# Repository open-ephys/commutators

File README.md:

> [!Important]  
> This repository has been split into dedicated repositories for each design:
>
>  - https://github.com/open-ephys/commutator-coax
>  - https://github.com/open-ephys/commutator-spi
>  - https://github.com/open-ephys/commutator-dual
>  - etc.
>
> Future commutator designs, issue tracking, etc. will take place in those repositories.
> This repository is deprecated.

# Torque-free commutators for orientation-aware headstages and miniscopes
The wide-spread availability of 6 degree of freedom pose tracking using
internal-measurement units (IMUs) allows continuous monitoring of an animal's
rotational state in an environment. This obviates the need for tether torque
measurements to drive an active commutator since the rotational state of the
animal is known in real-time, and the commutator can simply follow along. This
permits the use of extremely thin [coaxial
tethers](http://www.axon-cable.com/en/02_products/06_coaxial-cables/02/index.aspx)
that cannot function with a standard active commutator because they are too
flexible to translate rotational torque.

This commutator functions with headstages and miniscopes that provide
provide appropriate rotational tracking information. Currently
supported devices are next-generation, serialized headstages and miniscopes
such as [ONIX headstages](https://open-ephys.github.io/onix-docs/index.html), 
and UCLA Miniscope 4.0, and Open Ephys 3D low-profile SPI headstages.
However, this device operations completely independently from the headstage
itself, so can be used with any device that provides accurate, drift-free
rotational state. It can even be used without an IMU, e.g. using video-based
rotation tracking since its remote control interface is agnostic to how
rotational measurements are taken.

## Features
- Variants for high bandwidth RF links up to 18 GHz and low-bandwidth SPI cables
- Optical table & 80/20 rail mountable
- Remote control using JSON-encoded commands
- Manual control using capacitive sense buttons
- Indication LED
    - Can be completely turned off
- Advanced stepper driver (TMC2130)
    - Voltage-controlled for silent operation
    - Precise motion using step interpolation (256 uSteps/step)
- USB powered and controlled
    - Internal super-capacitor circuitry prevents loading the USB bus during
      motion

## Usage

**Note**: A high-quality, within-spec micro USB cable must be used when connecting 
the commutator to the host computer.

### LED
The LED tells you about the commutator state:

1. Flashing red (*Charging*): commutator is charging internal super-capacitors.
   All controls and motor operation are locked. Wait until this process
   completes to use the device. It can take up to 30 seconds.
1. Solid red (*Disabled*): commutator is disabled. Motor is turned off and will not
   turn or respond to button presses or external commands.
1. Green (*Enabled*): commutator is enabled and permits both remote and manual
   (button) turn control. Buttons take precedence over remote commands.

### Buttons
The front panel has four buttons.

- __Enable/Disable__: toggle commutator enable/disable.
    - *Disabled* (LED is red): All motor output will halt instantly, and motor
      driver is powered down. Pressing directional buttons in the stopped state
      will not work. All target turns provided via remote calls will be
      cleared, such that re-enable the motor will not result in the commutator
      re-engaging an old target position. In this state, pressing 
      the Enable/Disable button, or sending the approriate remote
      command, will enable the device.
    - *Enabled* (LED  green): When in the *enabled* state, the LED will be
      green and the motor can be turned via button presses or RPCs . In this
      state, pressing the Stop/Go button, or sending the approriate remote
      command, will instantly disable the device.

- __Directional__ (2x): Manually control the motor rotation in the
  direction indicated on each button when the commutator is *Enabled*. These
  inputs take precedence over and override ongoing remote motor control.  When
  pressed, all target turns provided via remote control will be cleared, such
  that releasing them will not result in the commutator re-engaging an old
  target position. Remote commands sent when a button is being pressed are
  ignored.

- __LED__: pressing the LED will toggled on and off (e.g for cases where it presents an
  unwanted visual stimulus).

### Remote control interface
When manual buttons are not being pressed, the commutator accepts JSON-encoded
commands over its serial interface. Here are examples of all commands that can
be sent:
```
{enable : true}     // Enable commutator (default = false)
{led : false}       // Turn off RGB LED (default = true)
{speed : 250}       // Set turn speed to 250 RPM (default = 50 RPM, valid ∈ (0, 500] RPM)
{turn : 1.1}        // 1.1 turns CW
{turn : -1.1}       // 1.1 turns CCW

// Example multi-command. Any combo can be used.
// In this case:
// 1. Turn LED off
// 1. Set speed to 25 RPM
// 2. Excecute 1.1 turns CC
// Ordering of commands does not matter, it is determined by the firmware
{led: false, speed: 25, turn : -1.1}
```
The communator state can be read using the `{print:}` command  which will
return a JSON object containing version, state, and motor parameters.

### Saving settings
All control and speed parameters, whether changed via the remote or manual
interface, are saved in non-volatile memory each time they are changed. The
device will start in the same state it was last used.

## Firmware
The controller firmware is located [here](./firmware/commutator). It runs on a
[Teensy lc](https://www.pjrc.com/store/teensylc.html). To compile
this firmware and program the microcontroller, you need the following
dependencies:

- [Arduino IDE](https://www.arduino.cc/en/Main/Software)
- [Teensyduino add-on](https://www.pjrc.com/teensy/td_download.html)
- [AccelStepper](https://www.airspayce.com/mikem/arduino/AccelStepper/)
- [Arduino JSON](https://arduinojson.org/)

The firmware can be uploaded to the device using the [Arduino
IDE](https://www.arduino.cc/en/Main/Software). _Note that you will need to add
the [Teensyduino add-on](https://www.pjrc.com/teensy/teensyduino.html) to to
the Arduino IDE to program the Teensy_. When installing Teensyduino, you should
opt to install all of the bundled libraries as well. This takes care of
installing `AccelStepper` library rather than having to install it manually.
ArduinoJSON can be installed through the Arduino IDE's package manager.

## Construction

### Bill of Materials
The BOM is located [here](https://docs.google.com/spreadsheets/d/1M2R0Q2-OuRHzctt05BxtA3hxNcCHtRZHORzCKElmG1Q/edit#gid=1283420334).

### Mechanical
The mechanical component of the commutator are as follows:

1. RF Rotary Joint
1. 2x reduction gears (3D-printed)
1. NEMA-11 Stepper Motor
1. Housing (3D-printed)
1. Some fasteners

Mechanical designs are located [here](./mechanical/). STL files for 3D printing
are located in the `stl` subdirectory. Links to purchase each of these
components, including 3D-printed parts, can be found on the BOM.

### Electronics
The board used to control the commutator consists of the following elements:

1. [Teensy LC](https://www.pjrc.com/store/teensylc.html) for receiving
   commands and controlling all circuit elements.
1. [TMC2130 stepper driver](https://www.analog.com/media/en/technical-documentation/data-sheets/TMC2130_datasheet_rev1.15.pdf) for driving the
   motor.
1. Super-capacitor charge system and step-up regulator for providing
   high-current capacity drive to the motor driver directly from USB.
1. RGB indicator LED.
1. Capacitive touch sensors on the back side of the PCB that serve as buttons
   for manual commutator control

Board designs and manufacturing files are located [here](./pcb/). 

## Hardware License
This license pertains to documents in the `control-board`, `mechanical`, and
`resources` subdirectory.

This work is licensed to Jonathan P. Newman and Jakob Voigts under CC BY-NC-SA
4.0. To view a copy of this license, visit
https://creativecommons.org/licenses/by-nc-sa/4.0

The creation of commercial products using the hardware documentation in this
repository is not permitted without an explicit, supplementary agreement
between the Licensor and the Licensee. Please get in touch if you are
interested in commercially distributing this tool.

## Software/Firmware License
This license pertains to documents in the source code in the `firmware`
subdirectory.

Copyright Jonathan P. Newman

Permission is hereby granted, free of charge, to any person obtaining a copy of
this software and associated documentation files (the "Software"), to deal in
the Software without restriction, including without limitation the rights to
use, copy, modify, merge, publish, distribute, sublicense, and/or sell copies
of the Software, and to permit persons to whom the Software is furnished to do
so, subject to the following conditions:

The above copyright notice and this permission notice shall be included in all
copies or substantial portions of the Software.

THE SOFTWARE IS PROVIDED "AS IS", WITHOUT WARRANTY OF ANY KIND, EXPRESS OR
IMPLIED, INCLUDING BUT NOT LIMITED TO THE WARRANTIES OF MERCHANTABILITY,
FITNESS FOR A PARTICULAR PURPOSE AND NONINFRINGEMENT. IN NO EVENT SHALL THE
AUTHORS OR COPYRIGHT HOLDERS BE LIABLE FOR ANY CLAIM, DAMAGES OR OTHER
LIABILITY, WHETHER IN AN ACTION OF CONTRACT, TORT OR OTHERWISE, ARISING FROM,
OUT OF OR IN CONNECTION WITH THE SOFTWARE OR THE USE OR OTHER DEALINGS IN THE
SOFTWARE.

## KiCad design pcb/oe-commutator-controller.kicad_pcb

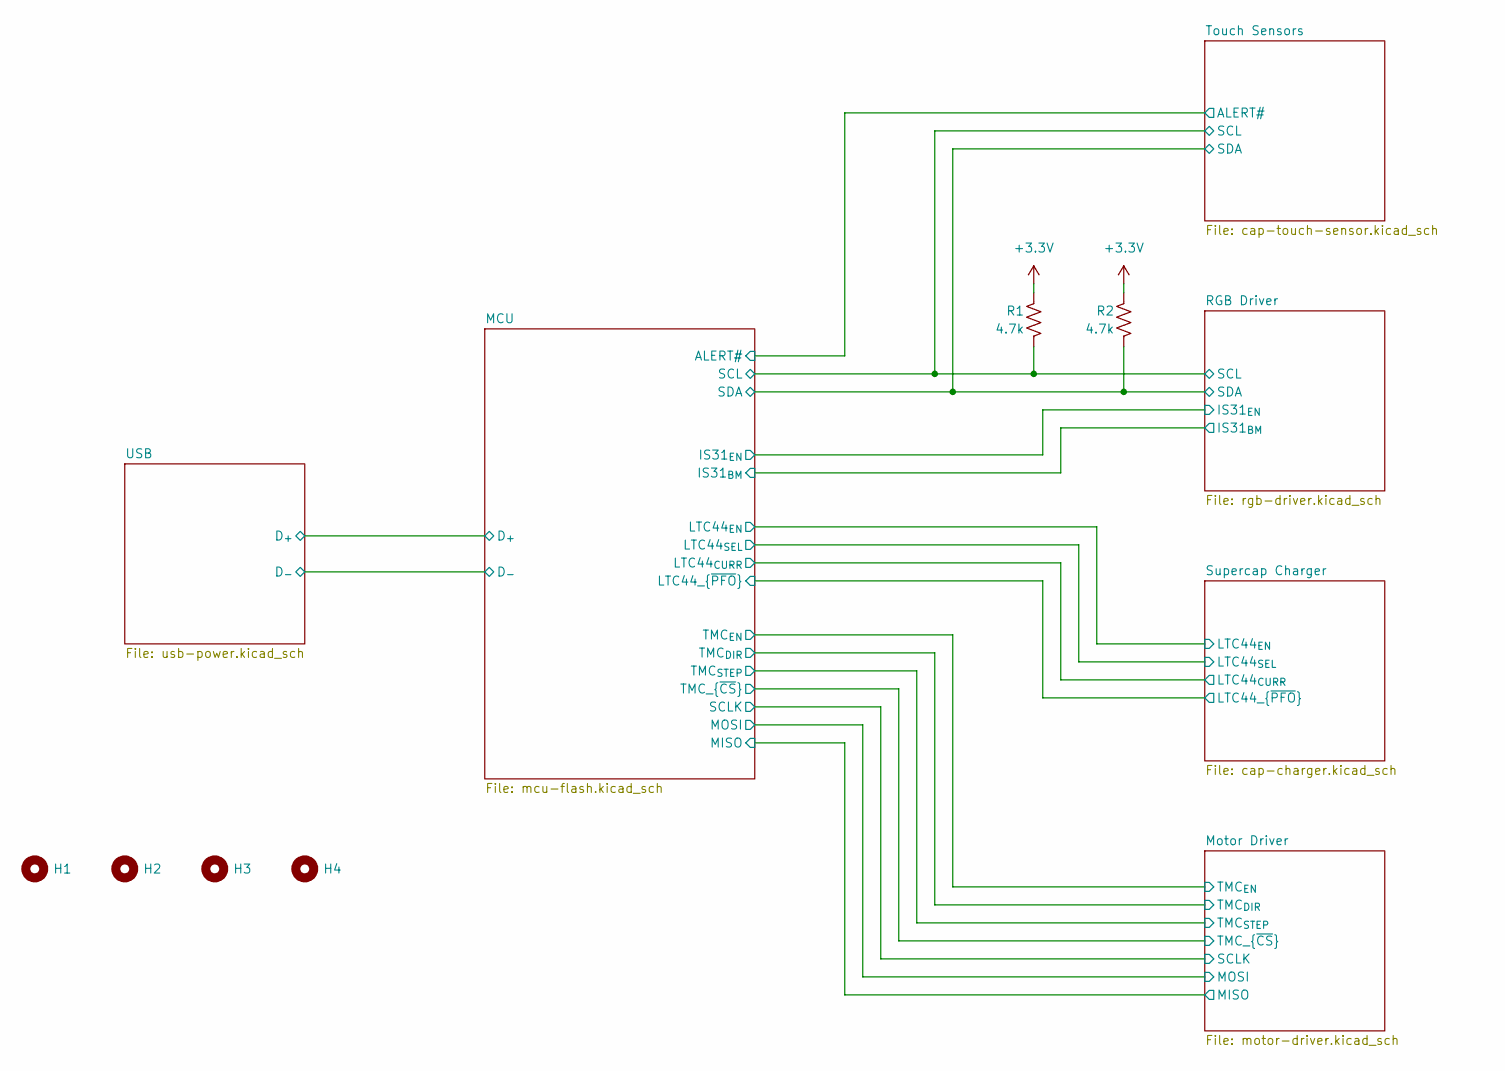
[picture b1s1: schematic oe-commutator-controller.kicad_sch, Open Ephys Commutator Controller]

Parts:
H1, H2, H3, H4: MountingHole_2.7mm_M2.5_ISO7380
R1, R2: 4.7k; R_0603_1608Metric

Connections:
+3.3V: R1.1, R2.1; also elsewhere on the board
/MCU/SCL: R1.2; also elsewhere on the board
/MCU/SDA: R2.2; also elsewhere on the board

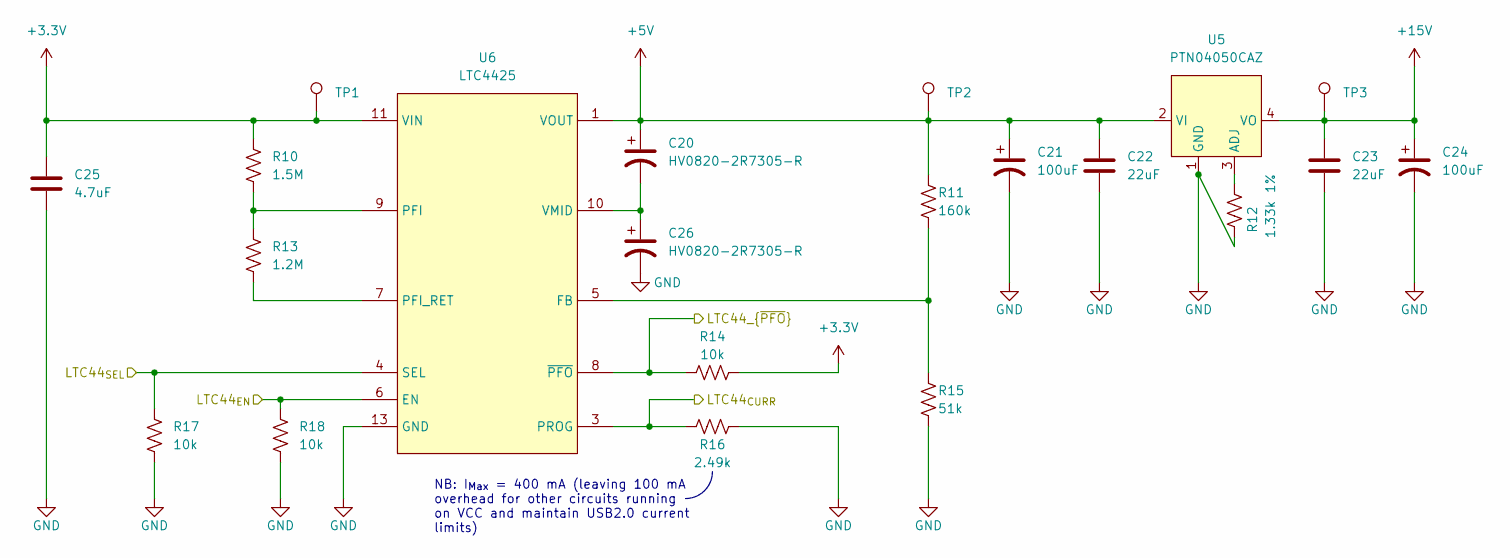
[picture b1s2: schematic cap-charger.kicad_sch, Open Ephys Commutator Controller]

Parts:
C20, C26: HV0820-2R7305-R; C_1210_3225Metric
C21, C24: 100uF; C_Elec_8x10.2
C22, C23: 22uF; C_1206_3216Metric
C25: 4.7uF; C_0805_2012Metric
R10: 1.5M; R_0603_1608Metric
R11: 160k; R_0603_1608Metric; Tolerance 1%
R12: 1.33k; R_0603_1608Metric; Tolerance 1%
R13: 1.2M; R_0603_1608Metric
R14, R17, R18: 10k; R_0603_1608Metric
R15: 51k; R_0603_1608Metric; Tolerance 1%
R16: 2.49k; R_0603_1608Metric
TP1, TP2, TP3: TestPoint_Pad_D2.0mm
U5: PTN04050CAZ; TI_R-PDSS_B4_SMD
U6: LTC4425; MSOP-12-1EP_3x4mm_P0.65mm_EP1.65x2.85mm

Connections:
+3.3V: C25.1, R10.1, R14.2, TP1.1, U6.11 (VIN), U6.12 (VIN); also elsewhere on the board
+5V: C20.1, C21.1, C22.1, R11.1, TP2.1, U5.2 (VI), U6.1 (VOUT), U6.2 (VOUT)
+15V: C23.1, C24.1, TP3.1, U5.4 (VO); also elsewhere on the board
/MCU/LTC44_{CURR}: R16.2, U6.3 (PROG); also elsewhere on the board
/MCU/LTC44_{EN}: R18.1, U6.6 (EN); also elsewhere on the board
/MCU/LTC44_{SEL}: R17.1, U6.4 (SEL); also elsewhere on the board
/MCU/LTC44_{~PFO}: R14.1, U6.8 (~PFO); also elsewhere on the board
unnamed: R12.1, U5.3 (ADJ)
unnamed: R11.2, R15.1, U6.5 (FB)
unnamed: R10.2, R13.1, U6.9 (PFI)
unnamed: R13.2, U6.7 (PFI_RET)
unnamed: C20.2, C26.1, U6.10 (VMID)

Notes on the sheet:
NB: I_{Max} = 400 mA (leaving 100 mA overhead for other circuits running on VCC and maintain USB2.0 current limits)

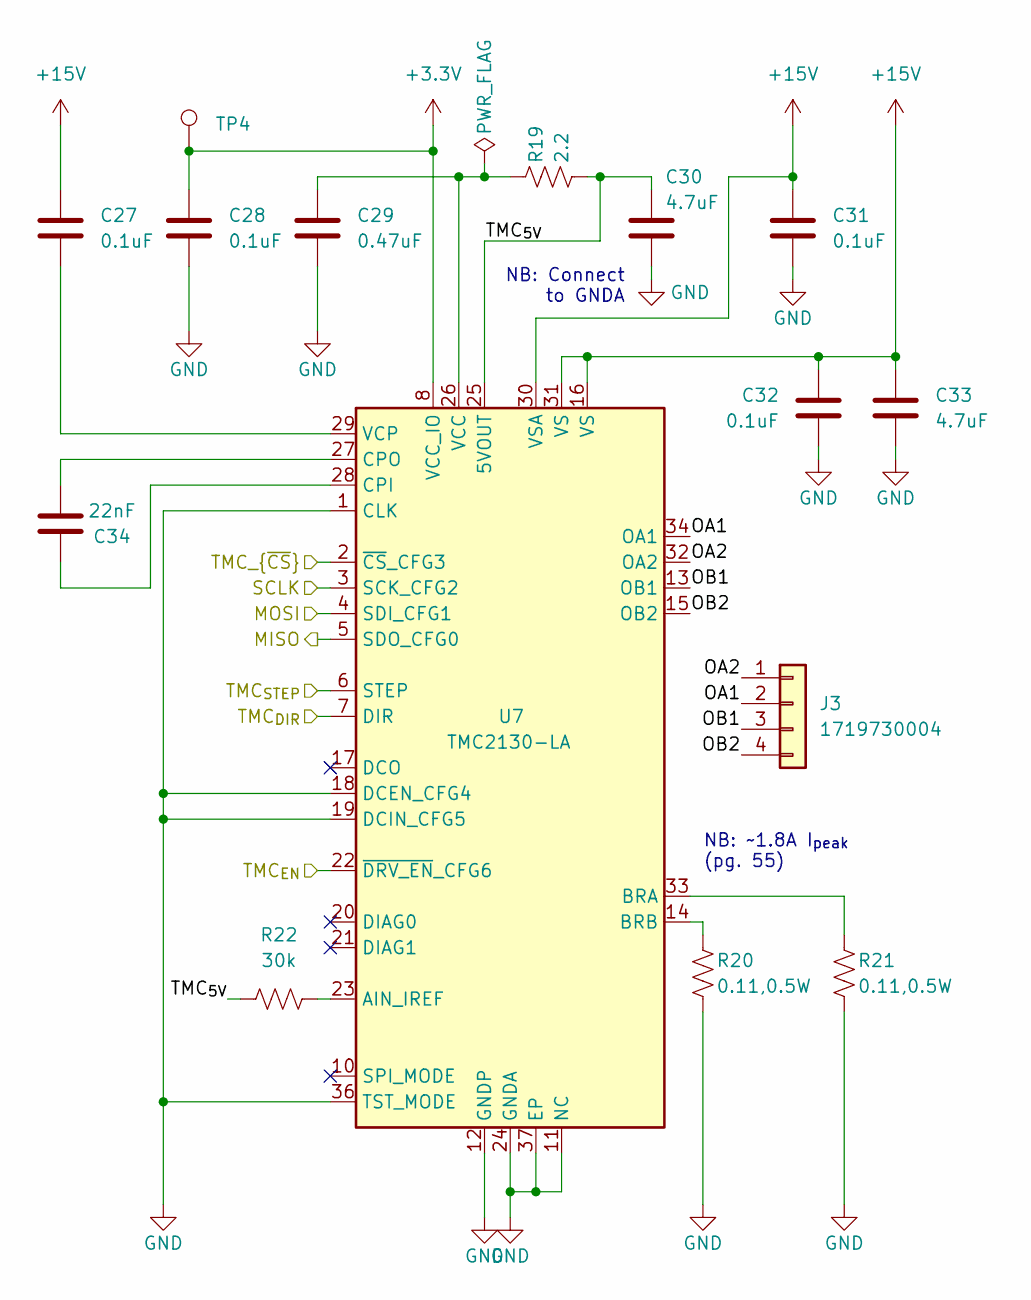
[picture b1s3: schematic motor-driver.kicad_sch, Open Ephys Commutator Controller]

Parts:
C27, C28, C31, C32: 0.1uF; C_0603_1608Metric; Voltage 50V
C29: 0.47uF; C_0805_2012Metric; Voltage 50V
C30, C33: 4.7uF; C_0805_2012Metric; Voltage 50V
C34: 22nF; C_0603_1608Metric; Voltage 50V
J3: 1719730004; MOLEX_1719730004_1x04_P2.54mm_Vert_Lock
R19: 2.2; R_0603_1608Metric
R20, R21: 0.11,0.5W; R_1206_3216Metric
R22: 30k; R_0603_1608Metric
TP4: TestPoint_Pad_D2.0mm
U7: TMC2130-LA; QFN-36-1EP_5x6mm_P0.5mm_EP3.6x4.1mm

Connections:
+3.3V: C28.1, TP4.1, U7.8 (VCC_IO); also elsewhere on the board
+15V: C27.2, C31.2, C32.2, C33.2, U7.16 (VS), U7.30 (VSA), U7.31 (VS); also elsewhere on the board
/MCU/MISO: U7.5 (SDO_CFG0); also elsewhere on the board
/MCU/MOSI: U7.4 (SDI_CFG1); also elsewhere on the board
/MCU/SCLK: U7.3 (SCK_CFG2); also elsewhere on the board
/MCU/TMC_{DIR}: U7.7 (DIR); also elsewhere on the board
/MCU/TMC_{EN}: U7.22 (~DRV_EN_CFG6); also elsewhere on the board
/MCU/TMC_{STEP}: U7.6 (STEP); also elsewhere on the board
/MCU/TMC_{~CS}: U7.2 (~CS_CFG3); also elsewhere on the board
/Motor Driver/OA1: J3.2, U7.34 (OA1)
/Motor Driver/OA2: J3.1, U7.32 (OA2)
/Motor Driver/OB1: J3.3, U7.13 (OB1)
/Motor Driver/OB2: J3.4, U7.15 (OB2)
/Motor Driver/TMC_{5V}: C30.2, R19.2, R22.1, U7.25 (5VOUT)
unnamed: R22.2, U7.23 (AIN_IREF)
unnamed: R21.1, U7.33 (BRA)
unnamed: R20.1, U7.14 (BRB)
unnamed: C34.2, U7.28 (CPI)
unnamed: C34.1, U7.27 (CPO)
unnamed: C29.1, R19.1, U7.26 (VCC)
unnamed: C27.1, U7.29 (VCP)

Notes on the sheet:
NB: ~1.8A I_{peak} (pg. 55)
NB: Connect to GNDA

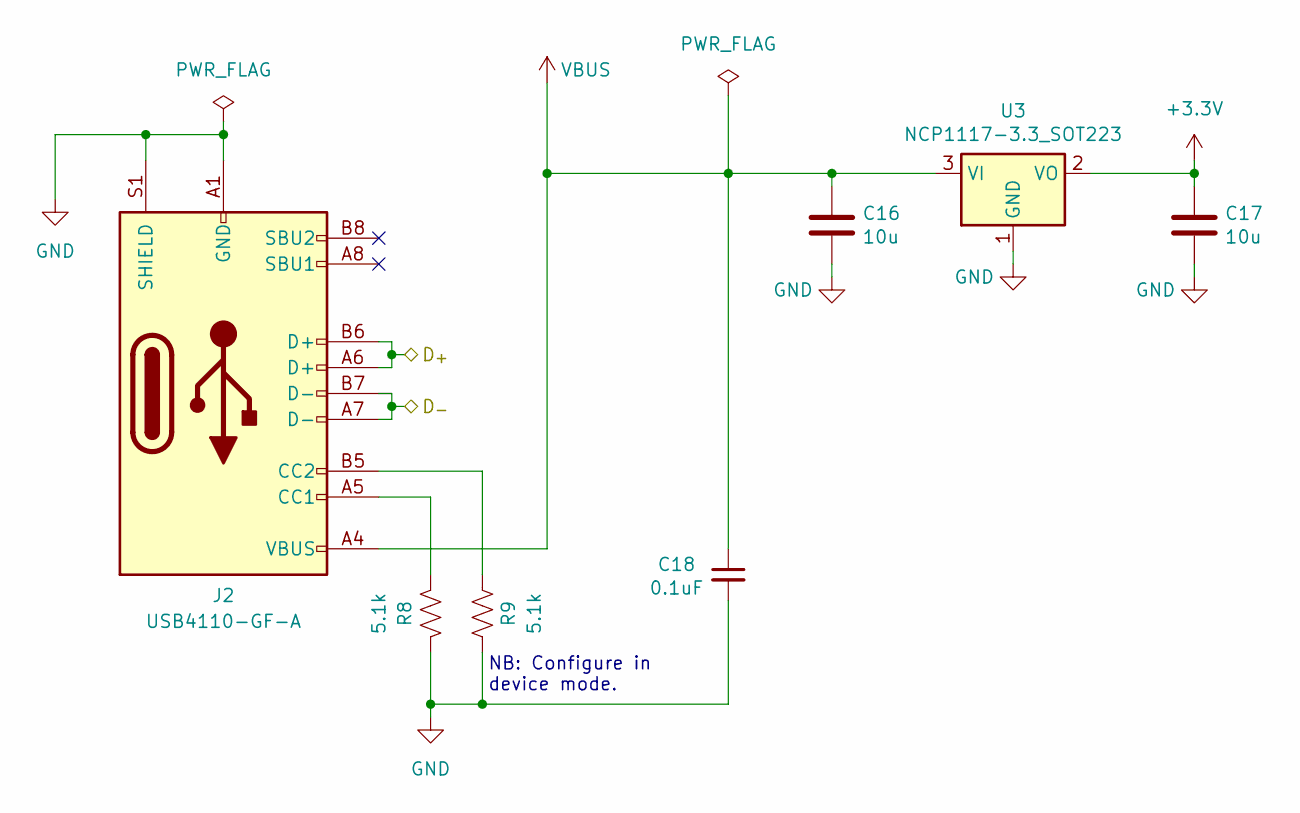
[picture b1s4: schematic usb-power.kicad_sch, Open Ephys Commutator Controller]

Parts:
C16, C17: 10u; C_0805_2012Metric
C18: 0.1uF; C_0603_1608Metric
J2: USB4110-GF-A; USB_C_Receptacle_GCT_USB4110
R8, R9: 5.1k; R_0402_1005Metric
U3: NCP1117-3.3_SOT223; SOT-223-3_TabPin2

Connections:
/MCU/D_{+}: J2.A6 (D+), J2.B6 (D+); also elsewhere on the board
/MCU/D_{-}: J2.A7 (D-), J2.B7 (D-); also elsewhere on the board
unnamed: C17.1, U3.2 (VO)
unnamed: J2.A5 (CC1), R8.2
unnamed: J2.B5 (CC2), R9.2
VBUS: C16.1, C18.1, J2.A4 (VBUS), J2.A9 (VBUS), J2.B4 (VBUS), J2.B9 (VBUS), U3.3 (VI); also elsewhere on the board

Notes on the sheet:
NB: Configure in device mode.

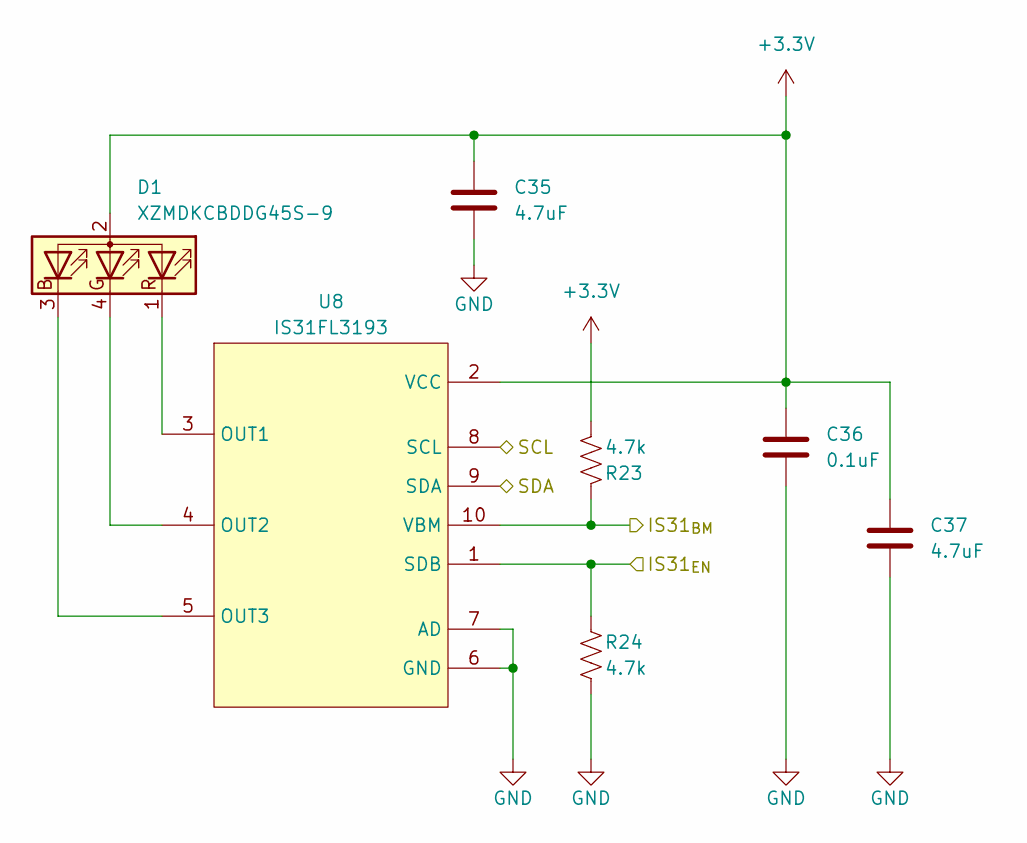
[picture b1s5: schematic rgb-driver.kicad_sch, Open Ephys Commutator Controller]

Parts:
C35, C37: 4.7uF; C_0805_2012Metric
C36: 0.1uF; C_0603_1608Metric; Voltage 50V
D1: XZMDKCBDDG45S-9; SUNLED_PLCC4-INV_3.2x2.8x1.9mm
R23, R24: 4.7k; R_0603_1608Metric
U8: IS31FL3193; DFN-10-1EP_3x3mm_P0.5mm_EP1.65x2.38mm

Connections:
+3.3V: C35.1, C36.1, C37.1, D1.2 (A), R23.2, U8.2 (VCC); also elsewhere on the board
/MCU/IS31_{BM}: R23.1, U8.10 (VBM); also elsewhere on the board
/MCU/IS31_{EN}: R24.1, U8.1 (SDB); also elsewhere on the board
/MCU/SCL: U8.8 (SCL); also elsewhere on the board
/MCU/SDA: U8.9 (SDA); also elsewhere on the board
unnamed: D1.3 (BK), U8.5 (OUT3)
unnamed: D1.4 (GK), U8.4 (OUT2)
unnamed: D1.1 (RK), U8.3 (OUT1)

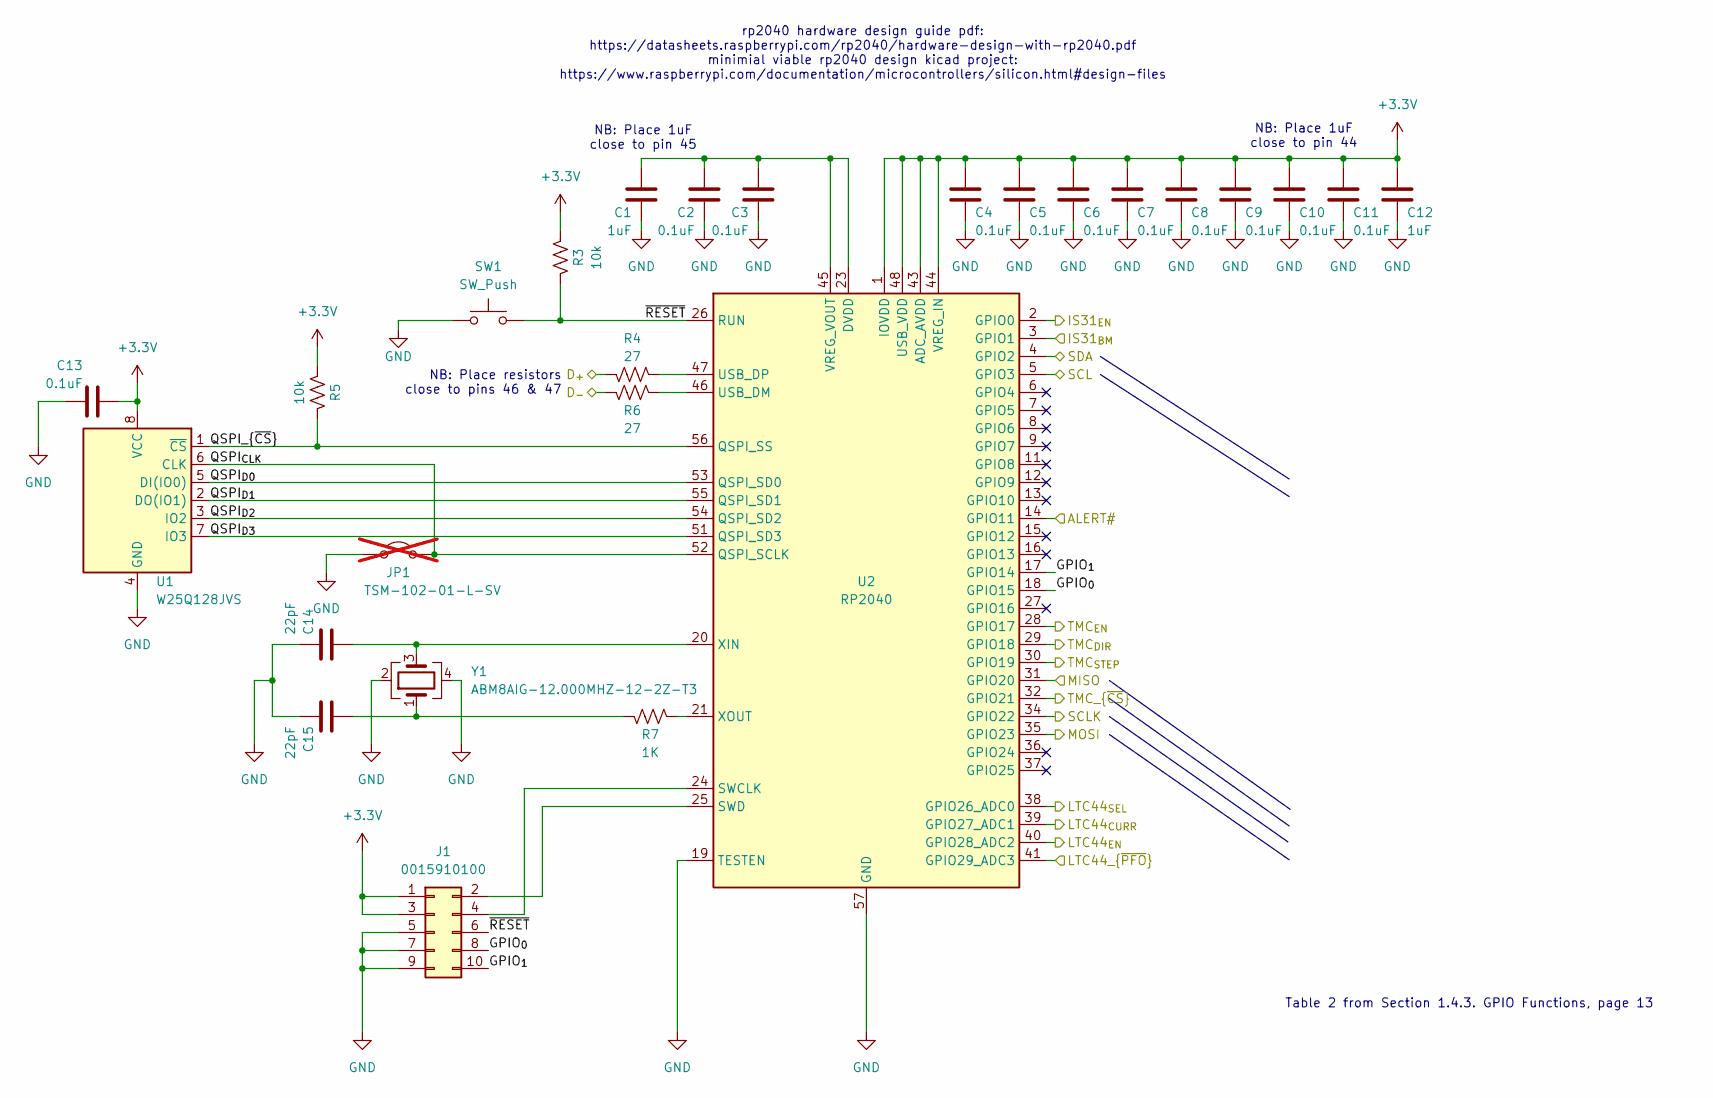
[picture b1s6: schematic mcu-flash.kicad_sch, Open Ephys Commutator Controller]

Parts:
C1, C12: 1uF; C_0603_1608Metric
C2, C3, C4, C5, C6, C7, C8, C9, C10, C11, C13: 0.1uF; C_0402_1005Metric
C14, C15: 22pF; C_0402_1005Metric
J1: 0015910100; PinHeader_2x05_P2.54mm_Vertical_SMD
JP1: TSM-102-01-L-SV; PinHeader_1x02_P2.54mm_Vertical_SMD_Pin1Left; not fitted
R3, R5: 10k; R_0402_1005Metric
R4, R6: 27; R_0402_1005Metric
R7: 1K; R_0402_1005Metric
SW1: SW_Push; SW_Push_1P1T_NO_CK_KMR2
U1: W25Q128JVS; SOIC-8_5.23x5.23mm_P1.27mm
U2: RP2040; QFN-56-1EP_7x7mm_P0.4mm_EP3.2x3.2mm
Y1: ABM8AIG-12.000MHZ-12-2Z-T3; Crystal_SMD_Abracon_ABM8AIG-4Pin_3.2x2.5mm

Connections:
+3.3V: C4.1, C5.1, C6.1, C7.1, C8.1, C9.1, C10.1, C11.1, C12.1, C13.1, J1.1, J1.3, R3.1, R5.1, U1.8 (VCC), U2.1 (IOVDD), U2.10 (IOVDD), U2.22 (IOVDD), U2.33 (IOVDD), U2.42 (IOVDD), U2.43 (ADC_AVDD), U2.44 (VREG_IN), U2.48 (USB_VDD), U2.49 (IOVDD); also elsewhere on the board
/MCU/ALERT#: U2.14 (GPIO11); also elsewhere on the board
/MCU/D_{+}: R4.2; also elsewhere on the board
/MCU/D_{-}: R6.2; also elsewhere on the board
/MCU/GPIO_{0}: J1.8, U2.18 (GPIO15)
/MCU/GPIO_{1}: J1.10, U2.17 (GPIO14)
/MCU/IS31_{BM}: U2.3 (GPIO1); also elsewhere on the board
/MCU/IS31_{EN}: U2.2 (GPIO0); also elsewhere on the board
/MCU/LTC44_{CURR}: U2.39 (GPIO27_ADC1); also elsewhere on the board
/MCU/LTC44_{EN}: U2.40 (GPIO28_ADC2); also elsewhere on the board
/MCU/LTC44_{SEL}: U2.38 (GPIO26_ADC0); also elsewhere on the board
/MCU/LTC44_{~PFO}: U2.41 (GPIO29_ADC3); also elsewhere on the board
/MCU/MISO: U2.31 (GPIO20); also elsewhere on the board
/MCU/MOSI: U2.35 (GPIO23); also elsewhere on the board
/MCU/QSPI_{CLK}: JP1.2 (B), U1.6 (CLK), U2.52 (QSPI_SCLK)
/MCU/QSPI_{D0}: U1.5 (DI(IO0)), U2.53 (QSPI_SD0)
/MCU/QSPI_{D1}: U1.2 (DO(IO1)), U2.55 (QSPI_SD1)
/MCU/QSPI_{D2}: U1.3 (IO2), U2.54 (QSPI_SD2)
/MCU/QSPI_{D3}: U1.7 (IO3), U2.51 (QSPI_SD3)
/MCU/QSPI_{~CS}: R5.2, U1.1 (~CS), U2.56 (QSPI_SS)
/MCU/SCL: U2.5 (GPIO3); also elsewhere on the board
/MCU/SCLK: U2.34 (GPIO22); also elsewhere on the board
/MCU/SDA: U2.4 (GPIO2); also elsewhere on the board
/MCU/TMC_{DIR}: U2.29 (GPIO18); also elsewhere on the board
/MCU/TMC_{EN}: U2.28 (GPIO17); also elsewhere on the board
/MCU/TMC_{STEP}: U2.30 (GPIO19); also elsewhere on the board
/MCU/TMC_{~CS}: U2.32 (GPIO21); also elsewhere on the board
unnamed: C15.1, R7.2, Y1.1
unnamed: J1.2, U2.25 (SWD)
unnamed: J1.4, U2.24 (SWCLK)
unnamed: R6.1, U2.46 (USB_DM)
unnamed: R4.1, U2.47 (USB_DP)
unnamed: C1.1, C2.1, C3.1, U2.23 (DVDD), U2.45 (VREG_VOUT), U2.50 (DVDD)
unnamed: C14.1, U2.20 (XIN), Y1.3
unnamed: R7.1, U2.21 (XOUT)

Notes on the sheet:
NB: Place resistors close to pins 46 & 47
NB: Place 1uF close to pin 44
NB: Place 1uF close to pin 45
rp2040 hardware design guide pdf: https://datasheets.raspberrypi.com/rp2040/hardware-design-with-rp2040.pdf minimial viable rp2040 design kicad project: https://www.raspberrypi.com/documentation/microcontrollers/silicon.html#design-files
Table 2 from Section 1.4.3. GPIO Functions, page 13

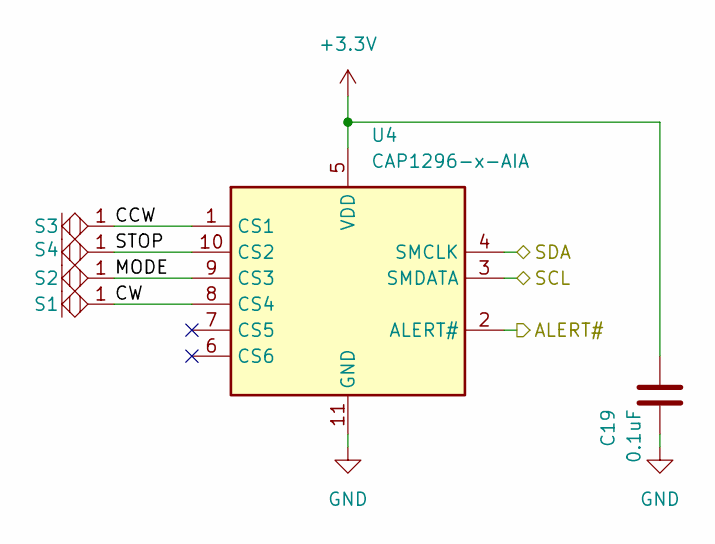
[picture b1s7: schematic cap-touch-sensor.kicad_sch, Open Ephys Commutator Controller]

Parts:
C19: 0.1uF; C_0402_1005Metric
S1, S2, S3, S4: Touch_Center_2mm
U4: CAP1296-x-AIA; DFN-10-1EP_3x3mm_P0.5mm_EP1.55x2.48mm

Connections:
+3.3V: C19.1, U4.5 (VDD); also elsewhere on the board
/MCU/ALERT#: U4.2 (ALERT#); also elsewhere on the board
/MCU/SCL: U4.3 (SMDATA); also elsewhere on the board
/MCU/SDA: U4.4 (SMCLK); also elsewhere on the board
/Touch Sensors/CCW: S3.1, U4.1 (CS1)
/Touch Sensors/CW: S1.1, U4.8 (CS4)
/Touch Sensors/MODE: S2.1, U4.9 (CS3)
/Touch Sensors/STOP: S4.1, U4.10 (CS2)

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
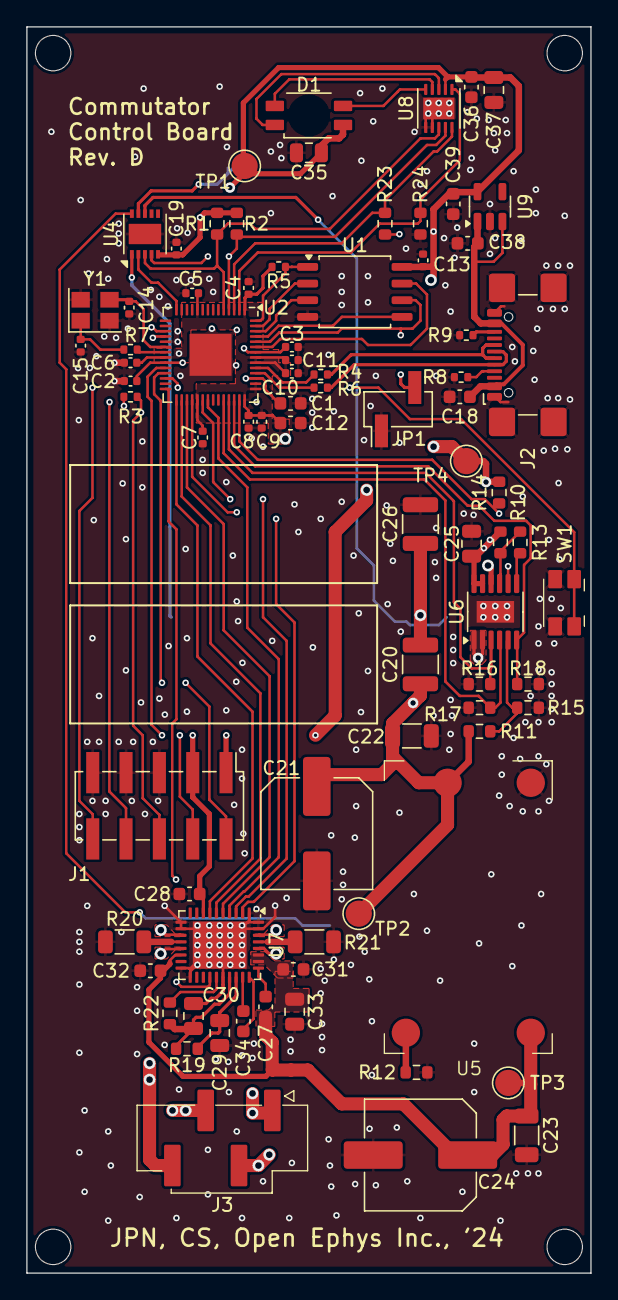
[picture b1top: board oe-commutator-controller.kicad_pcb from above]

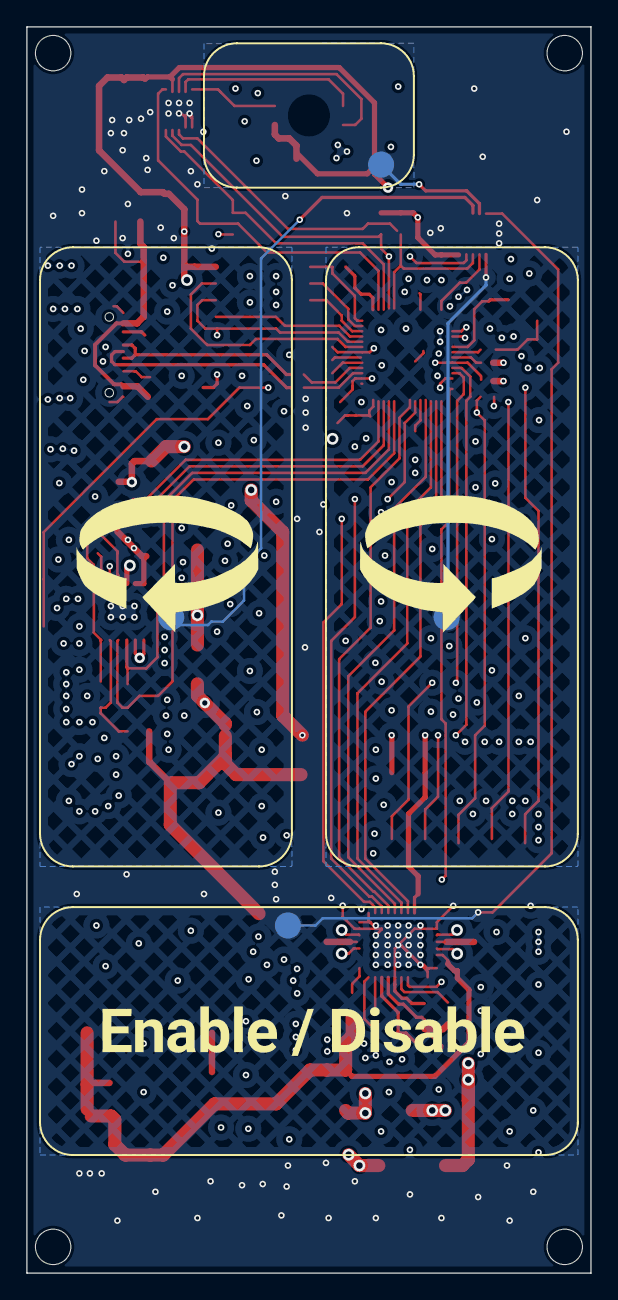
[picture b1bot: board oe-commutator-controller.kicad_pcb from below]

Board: 4 copper layers, 43.0 x 95.0 mm, 88 parts (4 on the bottom side), 66 nets.

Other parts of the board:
C38, C39: 1uF; C_0603_1608Metric
U9: AP2112K-3.3; SOT-23-5

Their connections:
+3.3V: C39.1, U9.5 (VOUT); also elsewhere on the board
VBUS: C38.1, U9.1 (VIN), U9.3 (EN); also elsewhere on the board

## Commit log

2018-12-17 initial commit 3d layout
2018-12-17 tweaked mounting
2018-12-18 updated commuttaor to use flanged rotary joint
2018-12-18 added pcb sizing info
2018-12-19 updated various parts
2019-01-07 Progress on commutator control board
    - Schematic is about complete with the exception of digital signal
    wiring, which should be done interactively to detangle wires
    - Added datasheets
    - Basic component placement
2019-01-07 Made housing 95mm tall to fit PCB
2019-01-09 Nearly complete control board
    - Silkscreen still needs work: button labels, device label, etc
2019-01-09 Completed control board
    - Pending review from jvoigts
2019-01-09 Small updates to control-board after review
    - Made sense of rotation direction icons less ambiguous and swapped
    positions
    - Moved push button back a bit
    - Remove copper layer between LED and top side of board
2019-01-10 Added stop/go button to control board
    - Added README
2019-01-10 Added fourth mode button on control board
    - Sits around RGB LED window
    - Also, increased min via drill size to 0.3mm which greatly decreases
    board cost
2019-01-10 Updated housing and gears - Added cutouts for teensy and reset switch - Made PCB housing deeper - Fixed mounting screw features - Added keyed features to gears - Reduced rotary joint gear ID to match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
2019-01-31 Adjusted id of larger gear to better fit commutator
2019-02-01 Commutator firmware
    - RPC interface
    - Manual, touch sensor interface
    - LED control
    - Saves settings
    - Etc, etc.
2019-02-01 Firmware updates and repo cleanup
    - Firware updates: manual, remote, and both control states now
    - Made all parameter values output referenced (to take care of 2x gear
    reduction)
    - Moved mechanical stuff to mechanical folder
2019-02-01 Added lincenses
    - Hardware is OHL v1.2
    - Software is beerware
2019-02-02 Updates to README, firmware, and control-board
    - Fixed mirrored pads for super capacitor charger
    - Switched Teensy LC for Teensy 3.2
    - Moved Teensy in 2mm so that housing does not need large cutout, but
    small one for micro USB
    - Fixed other small issues with the circuit
    - Some small changed to firmware: speed now provided directly in RPM
2019-02-02 Moved license to top level directory
2019-02-02 Update README.md
    Fix broken links.
2019-02-04 Tweaks to commutator housing - Made pcb compartment in housing deeper - Added extra height to bottom part so it can stand on surface
2019-02-14 Minor README update.
2019-06-02 Fixed firmware
    - Manual buttons work during remote turning
    - Stop button is immediate
2019-06-25 updated gear to fit the spinner RF joint
2019-09-13 Fix charging bug in firmware
    - The controller appeared to be unresponsive because it was not
    reporting when it was charging the supercaps. This commit fixes that
    - Also, I now turn off the controller 0.5 sec after the target turn has
    gone to 0. This may be a bad idea due to error accumulation.
    - Update the schematic of controller and provide new pdf
2019-09-22 Update gear_b.stl to match the current part
    - Fits the German rf rotary joint
2019-12-12 added dual channel doc
2019-12-23 Updates to README to get it ready for public release
    - Added licenses for hardware and software designs
    - Fully updated the BOM on google sheets and put links to in README
    - Update README to match the current firmware operation
2019-12-23 WIP 2 channel commutator
2019-12-24 initial design of dual-channel commutator housing
2020-01-17 Mechanical updates and added STLs
2020-09-22 Update README
    - Also move the CC BY-SA-NC 4.0 license for hardware
    - Add instructions for using {print:} command
    - Removed obsolete documentation
2020-09-22 Properly configure StealthChop mode for TMC2130
    - It was not actually on before
    - Also configure required control registers for this particular circuit
    (external current sense resistor, max run and hold current, max PWM
    characteristics, etc)
2020-09-26 Improvements in commutator firmware
    - When motor is stopped, driver is inactivated making the axle easy to
    turn
    - When motor is active but stopped, the driver continues to supplies a
    small amount of holding current so that error is not accumulated from
    repeated activation/inactivation of motor driver during stopped
    - The motor passively stops when a manual turn button is released to
2020-09-26 Small changes to the commutator driver board
    - No change in BOM or functionality
    - Added silkscreen outline to LED touch pad
    - Added OE logo
    - Remove license from silkscreen
2021-04-22 Small fixes to control board for production
    - Vias under LED driver were not symmetrical which caused delta-T during
    reflow and therefore bad settling of device. I made them symmetrical
    - Removed a couple random copper lines
2022-05-10 Update README.md
    - Fix BOM link
2022-10-17 Update README.md
    Add note about USB cable requirements to README
2023-03-20 Add mechanical design for 4 channels commutator
2023-03-20 Remove useless copies of dual chan
    Used as template to make the quad version. Not needed anymore
2023-03-20 Create readme.md
    Add readme to credit making lab and warn about potential issues
2023-03-24 add SPI enclosure prototype CAD files
2023-04-04 jon revisions + enclosed motor
2023-04-04 stl/step files for producing gears
2023-04-05 rev3
2023-04-05 added clearance for gear
2023-04-10 45 deg bevelled gear
2023-04-12 embiggened gears
2023-04-12 update production files
2023-07-17 jon's changes
    fillets added. I think this version was printed and sent
2023-07-19 production files updated to the ones printed by shapeways, source files not in sync
2023-09-11 createad notch for power button per production team's request
2023-09-14 widened m2.5 clearance holes for mounting nema stepper motor (2.7mm->3mm)
2023-10-25 Fix race condition resulting incorrect motor target
    - There was an issue with commands issued in quick succession, combined
    with the ability of the motor turn ISR to reset the target position to 0
    that caused steps to be lost in certain circumstances
    - The ISR has been minimized and now does not manipulate state outside
    of the motor object
    - target_turns is now never reset except when it is about to overflow
2023-11-06 Firmware version 1.3.0
    - Make threshold for button presses a function of their measured
    capacitance.
    - Turn off motor driver during initial supercap charging
    - Add diagnostic info to {print:}
2023-11-08 Fix gear ratio for dual coax commutator
    - Also reduced required capacitance change required to detect a button
    press
2023-11-16 Firmware version 1.4.0
    - Simplified button press logic following issues at SfN
2023-11-21 Control board rev. C
    - Move to KiCAD
    - Replace silent stepper stick with on-board circuit
2023-12-06 Board revision C
    - Sent to JLCPCB for testing
2023-12-19 Overhault button touch algorithm
    - Switch algorithm to differentiations -> integration method to drop
    intial capacitance of each button
    - Additionally, we do not take multiple readings and average but form an
    average over multiple calls to check the button capacitance, which
    results in much snappier interaciton with the panel
2024-01-23 Increase R_prog to 2.49k
    - This accounts for overhead current drawn from VCC by the Teensy and
    LED driver
2024-01-23 Add pdf of latest schematic
2024-01-24 Add teensy-type dependent filter for touch integration function
    - Touch sensor algorithm now filters capacitive deltas
    - Teensy 3.2 and Teensy LC have different capactive noise levels. A
    macro was added to dictate what teensy is being used and therefore
    what threshold to use for integrating capactive deltas
2024-05-01 Fix nan issue
    - When {turn:nan} was sent to the commutator it would completely freak
    out. We now filter for this situation.
2024-09-19 Update dual channel commutator enclosure
    - Enclose motor
    - Improve PCB mounting
    - Remove large hole that exposed Teensy
2024-09-26 Rev D Schematic
    - split schematic into several pages
    - replace teensy with rp2040
    - Add dedicated capacititave touch sensor ic
    - Replacec Micro-Usb with USB-C
2024-09-26 Remove redundant file
2024-09-26 Replaced through-hole components with SMD
    - Other small edits (e.g. optional jumper to force USB-boot)
2024-09-26 Add GPIO to programming header
2024-09-26 Initial Rev D PCB component layout
    - This is the initial component layout
    - Some traces are routed, but a review seems wise before I grind
    out routing the rest of the traces and start resolving DRC
2024-09-26 Move stickers, silkscreen label, & header
    - They were interfering in the previous commit
2024-09-27 Rev D PCB WIP for Review
    - Before going into further minutiae, get review
    - Components are laid out and routed
    - Fails DRC check, requires vias for better GND plane, there are traces
    in the outer keepout zone, remove S5?
2024-09-27 Revision D of controller PCB
    - Small changes during PCB review
    - This commit will be fabricated
2025-09-05 Update README.md
    - Add deprecation notice
